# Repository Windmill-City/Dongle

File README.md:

<h1 align="center">Dongle</h1>

<p align="center">
  CH570Q 2.4 GHz 无线串口透传模块
</p>

<p align="center">

</p>

> A CH570Q 2.4 GHz wireless UART dongle in a USB-A plug form factor.

## 简介

Dongle 是一块 USB-A 公头形态的无线串口模块，与 [Flasher](https://github.com/Windmill-City/Flasher) 配套使用：Flasher 负责供电、烧录和 USB/UART 桥接，Dongle 负责 2.4 GHz 无线链路。

固件在启动时采样 `PA0`/`PA1` 电平决定角色：

| 上电时 PA0/PA1 | 角色 | 行为 |
| --- | --- | --- |
| 都为低 | **master** | USB CDC（`1A86:5720`）+ 2.4 GHz 主机 |
| 其他 | **slave** | UART（PA0 TX / PA1 RX，默认 115200 8N1）+ 2.4 GHz 从机 |

裸机 C++17 固件，直接操作 CH570Q 寄存器，不依赖 WCH SDK。

## 特性

- **2.4 GHz 无线串口**：自定义链路层，带序列号、ACK、忙标志与 2 KiB 缓冲，支持双向流控。
- **master 模式**：USB CDC ↔ 无线链路，PC 端波特率等 LineCoding 通过 Reset 帧同步到从机。
- **slave 模式**：UART ↔ 无线链路；上电后 UART 处于 suspended，收到主机的 Reset 后按协商参数启用。
- **USB-A 公头**：直接插入 Flasher 或 PC 的 USB-A 口，无需接线。
- **免按键烧录**：通过 Flasher 自动进入 WCH ISP，完成擦除、写入与校验。
- **小尺寸**：11.5 × 16.4 mm，2 层板，板载 PCB 天线。

## 硬件

| 项目 | 参数 |
| --- | --- |
| MCU | WCH CH570Q（DFN-10） |
| 射频 | 2.4 GHz，板载 IFA PCB 天线 |
| 时钟 | 32 MHz 无源晶振 |
| 接口 | USB-A 公头 4P；PA0/PA1 复用 USB D-/D+ 与 UART |
| 指示 | LED（PA7，当前固件未驱动） |
| 供电 | USB 5 V |
| PCB | 11.5 × 16.4 mm，2 层，0.8 mm 厚 |

<p align="center">
  
  &nbsp;&nbsp;
  
</p>

<p align="center">
  左：正面（CH570Q、晶振、天线）　右：背面（USB-A 4P 触点）
</p>

## 构建

依赖 GNU Make 和 MounRiver Studio 3 自带的 WCH RISC-V GCC 工具链（默认路径可在 `firmware/Makefile` 中修改）：

```bash
cd firmware
make
```

输出位于 `firmware/build/`：

| 文件 | 说明 |
| --- | --- |
| `rf_uart_app.hex` | Intel HEX |
| `rf_uart_app.bin` | 裸二进制，Flasher 使用这个 |
| `rf_uart_app.elf` / `.map` | 调试符号与内存映射 |

Flash 窗口 240 KiB，RAM 12 KiB，镜像从 `0x00000000` 开始链接。

## 烧录

把 Dongle 插入 Flasher 的 USB-A 口，执行：

```bash
python ..\Flasher\firmware\tools\flasher.py flash firmware\build\rf_uart_app.bin --verify
```

Flasher 会自动上电进 Bootloader、解锁、擦除、写入并校验，**不需要按 BOOT 键或手动插拔**。完整流程和故障排查见 [docs/flasher.md](docs/flasher.md)。

## 使用

通过 Flasher 的 CDC 串口控制运行模式：

```bash
# master：USB CDC，PC 经 Flasher 透传
python ..\Flasher\firmware\tools\flasher.py master --monitor

# slave：UART，PC 经 Flasher 透传（默认 115200 8N1）
python ..\Flasher\firmware\tools\flasher.py slave --baud 115200 --monitor

# 仅控制电源：off / app / isp
python ..\Flasher\firmware\tools\flasher.py power app

# 查看状态，或从桥接模式返回命令模式
python ..\Flasher\firmware\tools\flasher.py info
python ..\Flasher\firmware\tools\flasher.py reset
```

烧录完成后目标默认以 **slave** 启动，不会自动枚举 USB；需要 USB 模式时执行 `master`。

## 仓库结构

```
.
├── Dongle.kicad_pro / .kicad_sch / .kicad_pcb   # KiCad 工程
├── Custom.kicad_sym / Custom.pretty             # 自定义符号与封装
├── production/                                  # Gerber、BOM、坐标、IPC 网表
├── docs/
│   ├── flasher.md                               # 烧录与调试指南
│   └── images/                                  # KiCad 3D 渲染图
└── firmware/
    ├── Makefile
    ├── ld/ch572.ld
    ├── include/ch572/                           # 寄存器、USB、UART、射频
    ├── src/                                     # 裸机固件与启动代码
    └── build/                                   # 编译产物
```

## 3D 渲染

图片由 KiCad 10 命令行渲染：

```bash
kicad-cli pcb render --width 1600 --height 1000 --quality high \
  --side top --background transparent --floor --perspective \
  --rotate "-35,0,25" --zoom 1.1 \
  -o docs/images/board-iso.png Dongle.kicad_pcb

kicad-cli pcb render --width 1200 --height 1500 --quality high \
  --side top --background transparent --floor --perspective \
  -o docs/images/board-top.png Dongle.kicad_pcb

kicad-cli pcb render --width 1200 --height 1500 --quality high \
  --side bottom --background transparent --floor --perspective \
  -o docs/images/board-bottom.png Dongle.kicad_pcb
```

`production/Dongle-1.1.zip` 为可直接送厂的 Gerber，BOM、坐标文件与 IPC 网表位于同一目录。

## 许可证

本项目采用 [Apache License 2.0](LICENSE) 开源。

Copyright 2026 Windmill_City

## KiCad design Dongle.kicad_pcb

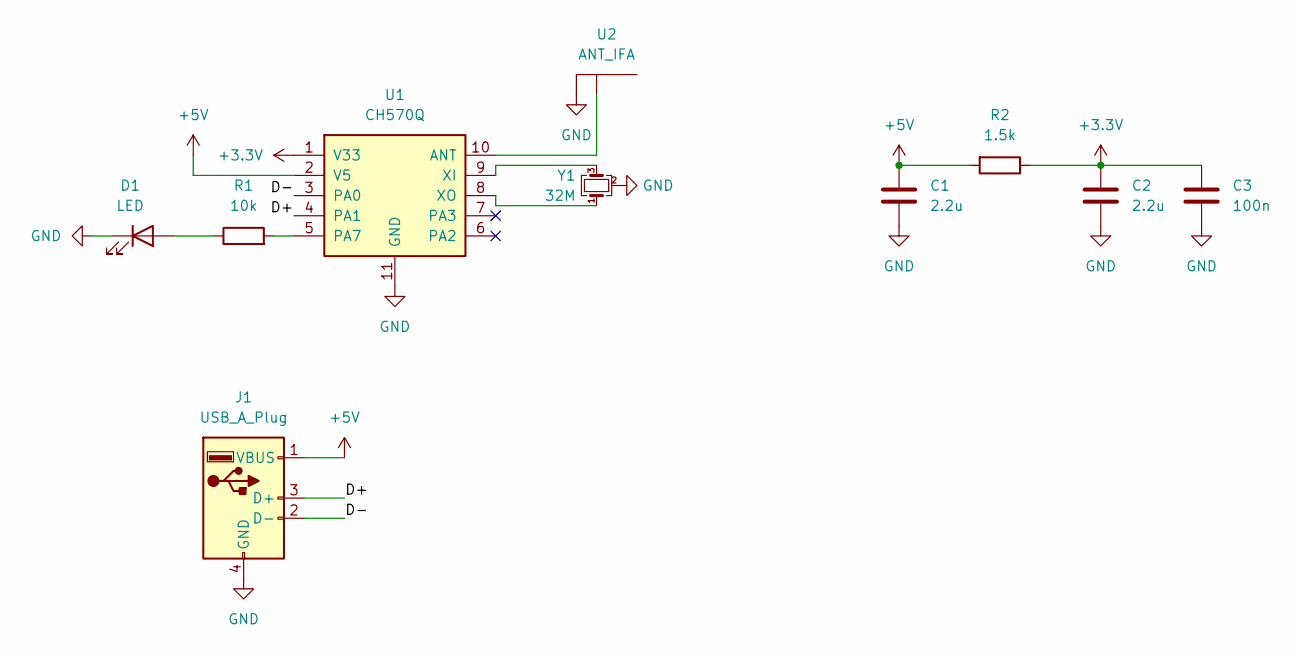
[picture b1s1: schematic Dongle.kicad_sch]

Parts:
C1, C2: 2.2u; C_0402_1005Metric
C3: 100n; C_0402_1005Metric
D1: LED; LED_0402_1005Metric
J1: USB_A_Plug; USB_A_Plug_4P
R1: 10k; R_0402_1005Metric
R2: 1.5k; R_0402_1005Metric
U1: CH570Q; DFN-10-1EP_3x3mm_P0.5mm_EP1.7x2.5mm
U2: ANT_IFA; ANT_IFA_Meander
Y1: 32M; Crystal_SMD_2016-4Pin_2.0x1.6mm

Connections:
+3.3V: C2.2, C3.2, R2.1, U1.1 (V33)
+5V: C1.2, J1.1 (VBUS), R2.2, U1.2 (V5)
/D+: J1.3 (D+), U1.4 (PA1)
/D-: J1.2 (D-), U1.3 (PA0)
GND: C1.1, C2.1, C3.1, D1.1 (K), J1.4 (GND), U1.11 (GND), U2.2 (GND), Y1.2 (G), Y1.4 (G)
unnamed: D1.2 (A), R1.1
unnamed: U1.10 (ANT), U2.1 (FEED)
unnamed: R1.2, U1.5 (PA7)
unnamed: U1.9 (XI), Y1.3
unnamed: U1.8 (XO), Y1.1

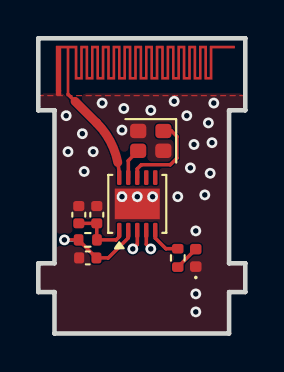
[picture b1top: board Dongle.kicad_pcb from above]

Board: 2 copper layers, 11.5 x 16.4 mm, 10 parts (1 on the bottom side), 10 nets.

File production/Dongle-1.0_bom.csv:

Designator,Footprint,Quantity,Value,LCSC Part #
"C1, C2",0402,2,2.2u,
D1,0402,1,LED,
J1,USB_A_Plug_4P,1,USB_A_Plug,
R1,0402,1,10k,
R2,0402,1,1.5k,
U1,DFN-10-1EP_3x3mm_P0.5mm_EP1.7x2.5mm,1,CH570Q,
U2,ANT_IFA_Meander,1,ANT_IFA,
Y1,Crystal_SMD_2016-4Pin_2.0x1.6mm,1,32M,

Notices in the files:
README.md:
License: Apache 2.0
